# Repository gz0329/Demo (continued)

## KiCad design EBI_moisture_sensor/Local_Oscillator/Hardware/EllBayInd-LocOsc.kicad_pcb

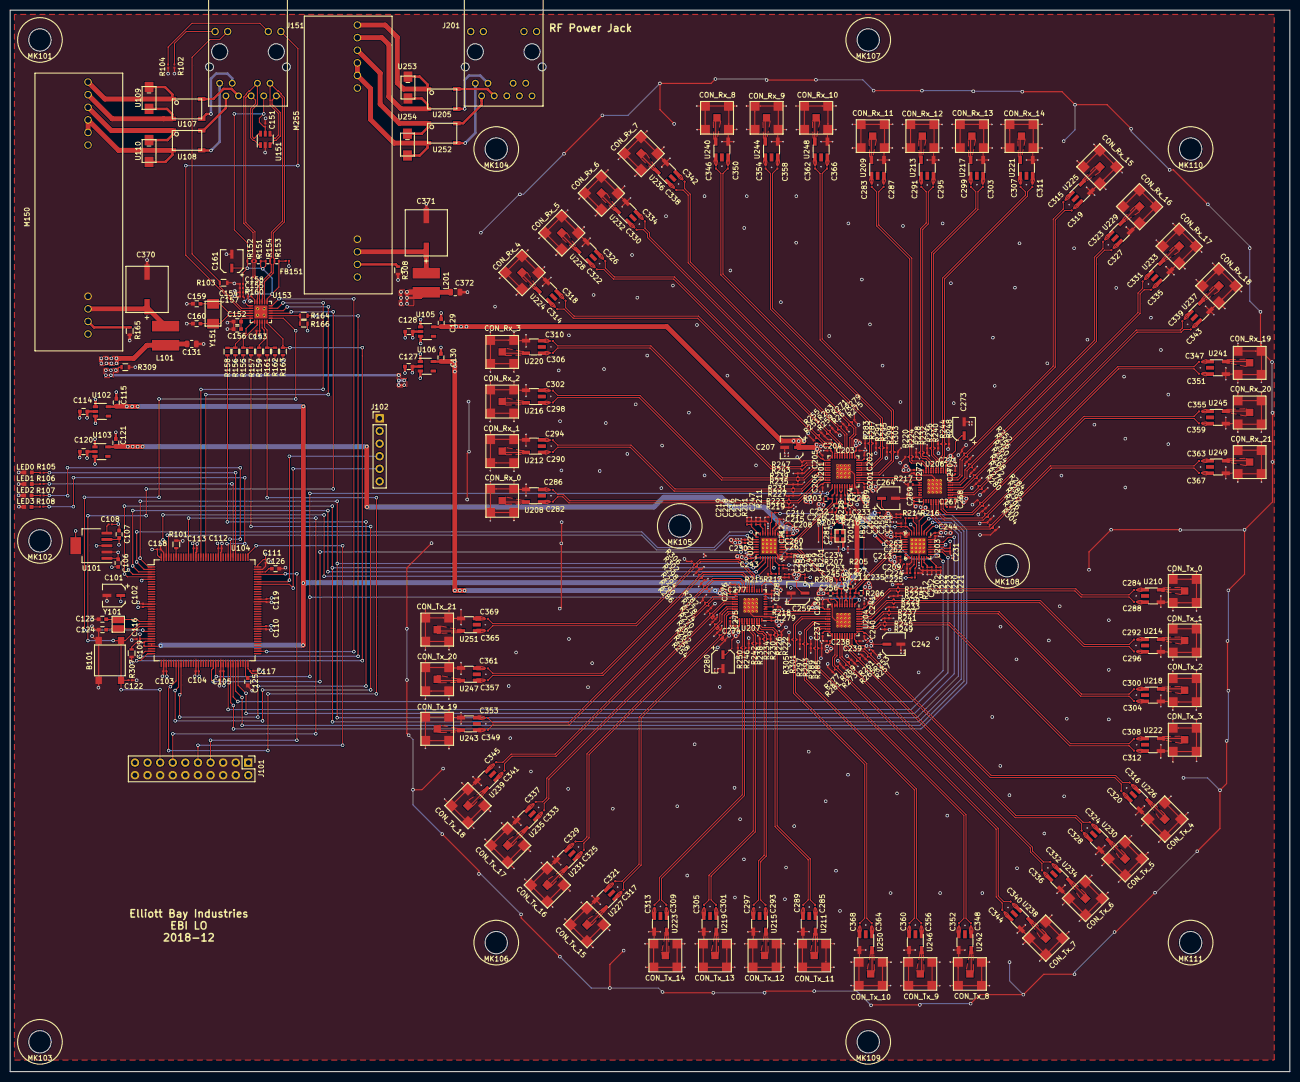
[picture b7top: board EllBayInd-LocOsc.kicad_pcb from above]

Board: 4 copper layers, 258.0 x 214.0 mm, 487 parts (0 on the bottom side), 356 nets.

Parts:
B101: Reset; Tactile_switch
C101, C161, C207, C242, C259, C264, C273, C280: 4.7uF; CP_Elec_4.3x4.3
C102, C103, C104, C105, C109, C110, C111, C112, C113, C116, C117, C118, C119, C122, C151, C153, C154, C155, C157, C158, C208, C209, C212, C213, C215, C217, C219, C220, C222, C224, C230, C231, C232, C235, C243, C244, C258, C261, C262, C265, C281: 100nF; C_0201_0603Metric
C106, C125, C126: 2.2uF; C_0603
C107, C114, C115, C120, C121, C127, C128, C129, C130, C156: 1uF; C_0603
C108: 0.01uF; C_0201_0603Metric
C123, C124: 4.3pF; C_0603
C131, C372: 10uF; C_0805_2012Metric
C152: 470pF; C_0603
C159, C160: 30pF; C_0603
C201, C202, C203, C204, C205, C206, C228, C229, C236, C237, C238, C239, C240, C241, C255, C256, C267, C268, C269, C270, C271, C272, C274, C275, C276, C277, C278, C279: 1nF; C_0201_0603Metric
C210, C211, C214, C216, C218, C221, C223, C225, C226, C227, C233, C234, C245, C246, C248, C251, C253, C254, C257, C260, C263, C266, C282, C283, C284, C285, C286, C287, C288, C289, C290, C291, C292, C293, C294, C295, C296, C297, C298, C299, C300, C301, C302, C303, C304, C305, C306, C307, C308, C309, C310, C311, C312, C313, C314, C315, C316, C317, C318, C319, C320, C321, C322, C323, C324, C325, C326, C327, C328, C329, C330, C331, C332, C333, C334, C335, C336, C337, C338, C339, C340, C341, C342, C343, C344, C345, C346, C347, C348, C349, C350, C351, C352, C353, C354, C355, C356, C357, C358, C359, C360, C361, C362, C363, C364, C365, C366, C367, C368, C369: 100pF; C_0201_0603Metric
C247, C252: 3.3pF; C_0201_0603Metric
C249, C250: 7.3pF; C_0201_0603Metric
C370, C371: 470uF; 470uF Cap
CON_Rx_0, CON_Rx_1, CON_Rx_2, CON_Rx_3, CON_Rx_4, CON_Rx_5, CON_Rx_6, CON_Rx_7, CON_Rx_8, CON_Rx_9, CON_Rx_10, CON_Rx_11, CON_Rx_12, CON_Rx_13, CON_Rx_14, CON_Rx_15, CON_Rx_16, CON_Rx_17, CON_Rx_18, CON_Rx_19, CON_Rx_20, CON_Rx_21: RF_SMA; SMAConnector
CON_Tx_0, CON_Tx_1, CON_Tx_2, CON_Tx_3, CON_Tx_4, CON_Tx_5, CON_Tx_6, CON_Tx_7, CON_Tx_8, CON_Tx_9, CON_Tx_10, CON_Tx_11, CON_Tx_12, CON_Tx_13, CON_Tx_14, CON_Tx_15, CON_Tx_16, CON_Tx_17, CON_Tx_18, CON_Tx_19, CON_Tx_20, CON_Tx_21: RF_SMA; SMAConnector
FB151, FB201, FB202: 600@100; L_0201_0603Metric
J101: SWD debugging; Program_Pin_Header
J102: Conn_01x06_UART1; PinHeader_1x06_P2.54mm_Vertical
J151, J201: RJ45_7499211122A; RJ45
L101, L201: 10uH; 10uH_Inductor
LED0, LED1, LED2, LED3: LED
M150, M255: AG9205S
MK101, MK102, MK103, MK104, MK105, MK106, MK107, MK108, MK109, MK110, MK111: Mounting_hole
R101, R103, R155, R156, R159, R162, R166: 10k; R_0603
R102, R104: 270; R_0201_0603Metric
R105, R106, R107, R108: 750; R_0201_0603Metric
R151, R152, R153, R154, R203, R204, R205, R206, R207, R208, R209, R210, R217, R218: 50; R_0402
R157, R158, R161, R164: 33; R_0603
R160: 12k1; R_0201_0603Metric
R163: 1k5; R_0603
R165, R308: 0; R_0603
R201, R202: 5.1k; R_0201_0603Metric
R211, R212: 91k; R_0201_0603Metric
R213, R214: 11.3k; R_0201_0603Metric
R215, R216: 33.2k; R_0201_0603Metric
R219, R220, R221, R222, R223, R224, R225, R226, R227, R228, R229, R230, R231, R232, R233, R234, R235, R236, R237, R238, R239, R240, R241, R242, R243, R244, R245, R246, R247, R248, R249, R250, R251, R252, R253, R254, R255, R256, R257, R258, R259, R260, R261, R262, R263, R264, R265, R266, R267, R268, R269, R270, R271, R272, R273, R274, R275, R276, R277, R278, R279, R280, R281, R282, R283, R284, R285, R286, R287, R288, R289, R290, R291, R292, R293, R294, R295, R296, R297, R298, R299, R300, R301, R302, R303, R304, R305, R306: 200; R_0201_0603Metric
R307, R309: Close; R_0603
U101: 5V_REG
U102, U103, U105, U106: 3V3_REG; 3V3REG
U104: STM32H743ZITx; MCU
U107, U108, U205, U252: MDB6S
U109, U110, U253, U254: SMAJ58CA
U151: USBLC6-4SC6; TVS-diode
U153: LAN8742A
U201, U204, U206, U207: ADCLK954
U202, U203: ADF4350
U208, U209, U210, U211, U212, U213, U214, U215, U216, U217, U218, U219, U220, U221, U222, U223, U224, U225, U226, U227, U228, U229, U230, U231, U232, U233, U234, U235, U236, U237, U238, U239, U240, U241, U242, U243, U244, U245, U246, U247, U248, U249, U250, U251: TC1-1-43+
Y101: 8 MHz; 8mhz_crystal
Y151: 25MHz; 25mhz_crystal
Y201: 24MHz; 24MhzCrystalOsc

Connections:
+3.3VA: C109.1, C115.1, FB201.1, FB202.1, U102.5, U104.32, U104.33, U202.16, U202.17, U203.16, U203.17
+3V3: C101.1, C102.1, C103.1, C104.1, C105.1, C110.1, C111.1, C112.1, C113.1, C116.1, C117.1, C118.1, C119.1, C121.1, C153.2, C208.1, C209.1, C212.1, C213.1, C230.1, C231.1, C232.1, C233.1, C234.1, C235.1, C243.1, C244.1, C281.1, FB151.2, J101.1, J101.2, R155.2, R156.2, R162.2, R163.2, R166.2, R203.2, R204.2, R205.2, R206.2, R207.1, R208.1, R209.1, R210.1, U103.5, U104.6, U104.17, U104.30, U104.39, U104.52, U104.62, U104.72, U104.84, U104.95, U104.108, U104.121, U104.131, U104.144, U153.9, U202.28, U202.32, U203.28, U203.32, Y201.4
+5V: C107.1, U101.4
/3.3V_FO_pair_0: C129.1, C201.1, C202.1, C203.1, C204.1, C205.1, C206.1, C207.1, C267.1, C268.1, C269.1, C270.1, C271.1, C272.1, C273.1, U105.5, U201.11, U201.20, U201.21, U201.30, U201.31, U201.40, U206.11, U206.20, U206.21, U206.30, U206.31, U206.40
/3.3V_FO_pair_1: C130.1, C236.1, C237.1, C238.1, C239.1, C240.1, C241.1, C242.1, C274.1, C275.1, C276.1, C277.1, C278.1, C279.1, C280.1, U106.5, U204.11, U204.20, U204.21, U204.30, U204.31, U204.40, U207.11, U207.20, U207.21, U207.30, U207.31, U207.40
/5.5V: C106.1, C114.1, C120.1, C131.2, L101.1, U101.1, U101.2, U102.1, U102.3, U103.1, U103.3
/5.5V_RF: C127.1, C128.1, C372.1, L201.1, U105.1, U105.3, U106.1, U106.3
/24MHz: U202.29, U203.29, Y201.3
/AVdd: C257.1, C258.1, C259.1, C260.1, C261.1, C262.1, C263.1, C264.1, C265.1, C266.1, FB201.2, FB202.2, U202.6, U202.10, U203.6, U203.10
/Common/CRS_DV: R161.2, U104.43
/Common/LED0: R105.2, U104.114
/Common/LED1: R106.2, U104.115
/Common/LED2: R107.2, U104.116
/Common/LED3: R108.2, U104.117
/Common/MDC: U104.27, U153.13
/Common/MDIO: R163.1, U104.36, U153.12
/Common/NRST: B101.3, B101.4, C122.1, J101.15, U104.25, U153.15
/Common/RX_D0: R157.2, U104.44
/Common/RX_D1: R158.2, U104.45
/Common/SWCLK: J101.9, U104.109
/Common/SWDIO: J101.7, U104.105
/Common/Sheet5C53D1CF/LED_G: J151.13, R103.1, U153.2
/Common/Sheet5C53D1CF/LED_Y: J151.11, U153.3
/Common/Sheet5C53D1CF/RX+: J151.4, R152.2, U151.6, U153.23
/Common/Sheet5C53D1CF/RX-: J151.5, R151.2, U151.1, U153.22
/Common/Sheet5C53D1CF/TX+: J151.1, R154.2, U151.3, U153.21
/Common/Sheet5C53D1CF/TX-: J151.2, R153.2, U151.4, U153.20
/Common/Sheet5C53D1CF/VC1+: J151.7, U107.4
/Common/Sheet5C53D1CF/VC1-: J151.8, U107.3
/Common/Sheet5C53D1CF/VC2+: J151.9, U108.4
/Common/Sheet5C53D1CF/VC2-: J151.10, U108.3
/Common/TRACESWO: J101.13, U104.133
/Common/TX_D0: U104.128, U153.17
/Common/TX_D1: U104.74, U153.18
/Common/TX_EN: U104.126, U153.16
/Common/UART1_RX: J102.4, U104.102
/Common/UART1_TX: J102.5, U104.101
/Common/nINT: R164.2, U104.35
/FIN0_N: C226.1, U201.2
/FIN0_P: C210.1, U201.3
/FIN1_N: C253.1, U204.6
/FIN1_P: C245.1, U204.7
/FIN2_N: C227.1, U204.2
/FIN2_P: C211.1, U204.3
/FIN3_N: C254.1, U201.6
/FIN3_P: C246.1, U201.7
/LO_RX_0_N: C286.2, R223.2, U201.38
/LO_RX_0_P: C282.2, R219.2, U201.39
/LO_RX_1_N: C294.2, R231.2, U201.36
/LO_RX_1_P: C290.2, R227.2, U201.37
/LO_RX_2_N: C302.2, R239.2, U201.34
/LO_RX_2_P: C298.2, R235.2, U201.35
/LO_RX_3_N: C310.2, R247.2, U201.32
/LO_RX_3_P: C306.2, R243.2, U201.33
/LO_RX_4_N: C318.2, R255.2, U201.28
/LO_RX_4_P: C314.2, R251.2, U201.29
/LO_RX_5_N: C326.2, R263.2, U201.26
/LO_RX_5_P: C322.2, R259.2, U201.27
/LO_RX_6_N: C334.2, R271.2, U201.24
/LO_RX_6_P: C330.2, R267.2, U201.25
/LO_RX_7_N: C342.2, R279.2, U201.22
/LO_RX_7_P: C338.2, R275.2, U201.23
/LO_RX_8_N: C350.2, R287.2, U201.18
/LO_RX_8_P: C346.2, R283.2, U201.19
/LO_RX_9_N: C358.2, R295.2, U201.16
/LO_RX_9_P: C354.2, R291.2, U201.17
/LO_RX_10_N: C366.2, R303.2, U201.14
/LO_RX_10_P: C362.2, R299.2, U201.15
/LO_RX_11_N: C287.2, R224.2, U206.38
/LO_RX_11_P: C283.2, R220.2, U206.39
/LO_RX_12_N: C295.2, R232.2, U206.36
/LO_RX_12_P: C291.2, R228.2, U206.37
/LO_RX_13_N: C303.2, R240.2, U206.34
/LO_RX_13_P: C299.2, R236.2, U206.35
/LO_RX_14_N: C311.2, R248.2, U206.32
/LO_RX_14_P: C307.2, R244.2, U206.33
/LO_RX_15_N: C319.2, R256.2, U206.28
/LO_RX_15_P: C315.2, R252.2, U206.29
/LO_RX_16_N: C327.2, R264.2, U206.26
/LO_RX_16_P: C323.2, R260.2, U206.27
/LO_RX_17_N: C335.2, R272.2, U206.24
/LO_RX_17_P: C331.2, R268.2, U206.25
/LO_RX_18_N: C343.2, R280.2, U206.22
/LO_RX_18_P: C339.2, R276.2, U206.23
/LO_RX_19_N: C351.2, R288.2, U206.18
/LO_RX_19_P: C347.2, R284.2, U206.19
/LO_RX_20_N: C359.2, R296.2, U206.16
/LO_RX_20_P: C355.2, R292.2, U206.17
/LO_RX_21_N: C367.2, R304.2, U206.14
/LO_RX_21_P: C363.2, R300.2, U206.15
/LO_TX_0_N: C288.2, R225.2, U204.38
/LO_TX_0_P: C284.2, R221.2, U204.39
/LO_TX_1_N: C296.2, R233.2, U204.36
/LO_TX_1_P: C292.2, R229.2, U204.37
/LO_TX_2_N: C304.2, R241.2, U204.34
/LO_TX_2_P: C300.2, R237.2, U204.35
/LO_TX_3_N: C312.2, R249.2, U204.32
/LO_TX_3_P: C308.2, R245.2, U204.33
/LO_TX_4_N: C320.2, R257.2, U204.28
/LO_TX_4_P: C316.2, R253.2, U204.29
/LO_TX_5_N: C328.2, R265.2, U204.26
/LO_TX_5_P: C324.2, R261.2, U204.27
/LO_TX_6_N: C336.2, R273.2, U204.24
/LO_TX_6_P: C332.2, R269.2, U204.25
/LO_TX_7_N: C344.2, R281.2, U204.22
/LO_TX_7_P: C340.2, R277.2, U204.23
/LO_TX_8_N: C352.2, R289.2, U204.18
/LO_TX_8_P: C348.2, R285.2, U204.19
/LO_TX_9_N: C360.2, R297.2, U204.16
/LO_TX_9_P: C356.2, R293.2, U204.17
/LO_TX_10_N: C368.2, R305.2, U204.14
/LO_TX_10_P: C364.2, R301.2, U204.15
/LO_TX_11_N: C289.2, R226.2, U207.38
/LO_TX_11_P: C285.2, R222.2, U207.39
/LO_TX_12_N: C297.2, R234.2, U207.36
/LO_TX_12_P: C293.2, R230.2, U207.37
/LO_TX_13_N: C305.2, R242.2, U207.34
/LO_TX_13_P: C301.2, R238.2, U207.35
/LO_TX_14_N: C313.2, R250.2, U207.32
/LO_TX_14_P: C309.2, R246.2, U207.33
/LO_TX_15_N: C321.2, R258.2, U207.28
/LO_TX_15_P: C317.2, R254.2, U207.29
/LO_TX_16_N: C329.2, R266.2, U207.26
/LO_TX_16_P: C325.2, R262.2, U207.27
/LO_TX_17_N: C337.2, R274.2, U207.24
/LO_TX_17_P: C333.2, R270.2, U207.25
/LO_TX_18_N: C345.2, R282.2, U207.22
/LO_TX_18_P: C341.2, R278.2, U207.23
/LO_TX_19_N: C353.2, R290.2, U207.18
/LO_TX_19_P: C349.2, R286.2, U207.19
/LO_TX_20_N: C361.2, R298.2, U207.16
/LO_TX_20_P: C357.2, R294.2, U207.17
/LO_TX_21_N: C369.2, R306.2, U207.14
/LO_TX_21_P: C365.2, R302.2, U207.15
/RF_VC1+: J201.7, U205.4
/RF_VC1-: J201.8, U205.3
/RF_VC2+: J201.9, U252.4
/RF_VC2-: J201.10, U252.3
/SEL_SYNTH_1: U104.59, U201.1, U204.1
/SPI4_MOSI: U104.5, U202.2, U203.2
/SPI4_SCK: U104.1, U202.1, U203.1
/SYNTH0_EN: U104.142, U202.4
/SYNTH0_LD: U104.2, U202.25
/SYNTH0_MUXOUT: U104.58, U202.30
/SYNTH1_EN: U104.65, U203.4
/SYNTH1_LD: U104.66, U203.25
/SYNTH1_MUXOUT: U104.68, U203.30
/Vtune0: C247.1, R211.1, U202.20
/Vtune1: C252.1, R212.1, U203.20
/~SYNTH0_CS: U104.3, U202.3
/~SYNTH0_PDBrf: U104.141, U202.26
/~SYNTH1_CS: U104.67, U203.3
/~SYNTH1_PDBrf: U104.64, U203.26
GND: B101.1, B101.2, C101.2, C102.2, C103.2, C104.2, C105.2, C110.2, C111.2, C112.2, C113.2, C116.2, C117.2, C118.2, C119.2, C122.2, C123.2, C124.2, C125.2, C126.2, C131.1, C151.1, C152.1, C153.1, C154.1, C155.1, C156.1, C157.1, C158.1, C159.1, C160.1, C161.2, C201.2, C202.2, C203.2, C204.2, C205.2, C206.2, C207.2, C208.2, C209.2, C212.2, C213.2, C214.2, C215.2, C216.2, C217.2, C218.2, C219.2, C220.2, C221.2, C222.2, C223.2, C224.2, C225.2, C228.1, C229.1, C230.2, C231.2, C232.2, C233.2, C234.2, C235.2, C236.2, C237.2, C238.2, C239.2, C240.2, C241.2, C242.2, C243.2, C244.2, C247.2, C249.2, C250.2, C252.2, C255.1, C256.1, C257.2, C258.2, C259.2, C260.2, C261.2, C262.2, C263.2, C264.2, C265.2, C266.2, C267.2, C268.2, C269.2, C270.2, C271.2, C272.2, C273.2, C274.2, C275.2, C276.2, C277.2, C278.2, C279.2, C280.2, C281.2, C370.2, C371.2, C372.2, CON_Rx_0.2, CON_Rx_1.2, CON_Rx_2.2, CON_Rx_3.2, CON_Rx_4.2, CON_Rx_5.2, CON_Rx_6.2, CON_Rx_7.2, CON_Rx_8.2, CON_Rx_9.2, CON_Rx_10.2, CON_Rx_11.2, CON_Rx_12.2, CON_Rx_13.2, CON_Rx_14.2, CON_Rx_15.2, CON_Rx_16.2, CON_Rx_17.2, CON_Rx_18.2, CON_Rx_19.2, CON_Rx_20.2, CON_Rx_21.2, CON_Tx_0.2, CON_Tx_1.2, CON_Tx_2.2, CON_Tx_3.2, CON_Tx_4.2, CON_Tx_5.2, CON_Tx_6.2, CON_Tx_7.2, CON_Tx_8.2, CON_Tx_9.2, CON_Tx_10.2, CON_Tx_11.2, CON_Tx_12.2, CON_Tx_13.2, CON_Tx_14.2, CON_Tx_15.2, CON_Tx_16.2, CON_Tx_17.2, CON_Tx_18.2, CON_Tx_19.2, CON_Tx_20.2, CON_Tx_21.2, J101.3, J101.4, J101.5, J101.6, J101.8, J101.10, J101.12, J101.14, J101.16, J101.18, J101.20, J102.1, LED0.1, LED1.1, LED2.1, LED3.1, M150.7, M255.7, R101.2, R102.2, R103.2, R104.2, R159.2, R160.1, R165.1, R201.1, R202.1, R215.1, R216.1, R217.2, R218.2, R219.1, R220.1, R221.1, R222.1, R223.1, R224.1, R225.1, R226.1, R227.1, R228.1, R229.1, R230.1, R231.1, R232.1, R233.1, R234.1, R235.1, R236.1, R237.1, R238.1, R239.1, R240.1, R241.1, R242.1, R243.1, R244.1, R245.1, R246.1, R247.1, R248.1, R249.1, R250.1, R251.1, R252.1, R253.1, R254.1, R255.1, R256.1, R257.1, R258.1, R259.1, R260.1, R261.1, R262.1, R263.1, R264.1, R265.1, R266.1, R267.1, R268.1, R269.1, R270.1, R271.1, R272.1, R273.1, R274.1, R275.1, R276.1, R277.1, R278.1, R279.1, R280.1, R281.1, R282.1, R283.1, R284.1, R285.1, R286.1, R287.1, R288.1, R289.1, R290.1, R291.1, R292.1, R293.1, R294.1, R295.1, R296.1, R297.1, R298.1, R299.1, R300.1, R301.1, R302.1, R303.1, R304.1, R305.1, R306.1, R307.2, R308.2, R309.1, U104.16, U104.38, U104.51, U104.61, U104.83, U104.94, U104.107, U104.120, U104.130, U104.143, U151.2, U153.25, U201.10, U201.41, U202.8, U202.9, U202.11, U202.18, U202.21, U202.27, U202.31, U202.33, U203.8, U203.9, U203.11, U203.18, U203.21, U203.27, U203.31, U203.33, U204.10, U204.41, U206.1, U206.10, U206.41, U207.1, U207.10, U207.41, U208.4, U209.4, U210.4, U211.4, U212.4, U213.4, U214.4, U215.4, U216.4, U217.4, U218.4, U219.4, U220.4, U221.4, U222.4, U223.4, U224.4, U225.4, U226.4, U227.4, U228.4, U229.4, U230.4, U231.4, U232.4, U233.4, U234.4, U235.4, U236.4, U237.4, U238.4, U239.4, U240.4, U241.4, U242.4, U243.4, U244.4, U245.4, U246.4, U247.4, U248.4, U249.4, U250.4, U251.4, Y201.2
GNDA: C109.2, R307.1, U104.31
GNDPWR: C106.2, C107.2, C108.2, C114.2, C115.2, C120.2, C121.2, C127.2, C128.2, C129.2, C130.2, R309.2, U101.3, U101.6, U102.2, U103.2, U105.2, U106.2
unnamed: C108.1, U101.5
unnamed: C123.1, U104.23, Y101.1
unnamed: C124.1, U104.24, Y101.2
unnamed: C125.1, U104.71
unnamed: C126.1, U104.106
unnamed: C151.2, C154.2, C155.2, C157.2, C158.2, C161.1, FB151.1, J151.3, R151.1, R152.1, R153.1, R154.1, U151.5, U153.1, U153.19
unnamed: C152.2, C156.2, U153.6
unnamed: C159.2, U153.4, Y151.2
unnamed: C160.2, U153.5, Y151.1
unnamed: C210.2, R204.1, U202.14
unnamed: C211.2, R205.1, U203.14
unnamed: C214.1, C215.1, U202.19
unnamed: C216.1, C217.1, U202.23
unnamed: C218.1, C219.1, U202.24
unnamed: C220.1, C221.1, U203.24
unnamed: C222.1, C223.1, U203.23
unnamed: C224.1, C225.1, U203.19
unnamed: C226.2, R203.1, U202.15
unnamed: C227.2, R206.1, U203.15
unnamed: C228.2, U201.4, U201.5
unnamed: C229.2, U201.8, U201.9
unnamed: C245.2, R208.2, U202.12
unnamed: C246.2, R209.2, U203.12
unnamed: C248.1, C249.1, R211.2, U202.7
unnamed: C248.2, R213.2
unnamed: C250.1, C251.1, R212.2, U203.7
unnamed: C251.2, R214.2
unnamed: C253.2, R207.2, U202.13
unnamed: C254.2, R210.2, U203.13
unnamed: C255.2, U204.4, U204.5
unnamed: C256.2, U204.8, U204.9
unnamed: C282.1, U208.1
unnamed: C283.1, U209.1
unnamed: C284.1, U210.1
unnamed: C285.1, U211.1
unnamed: C286.1, U208.3
unnamed: C287.1, U209.3
unnamed: C288.1, U210.3
unnamed: C289.1, U211.3
unnamed: C290.1, U212.1
unnamed: C291.1, U213.1
unnamed: C292.1, U214.1
unnamed: C293.1, U215.1
unnamed: C294.1, U212.3
unnamed: C295.1, U213.3
unnamed: C296.1, U214.3
unnamed: C297.1, U215.3
unnamed: C298.1, U216.1
unnamed: C299.1, U217.1
unnamed: C300.1, U218.1
unnamed: C301.1, U219.1
unnamed: C302.1, U216.3
unnamed: C303.1, U217.3
unnamed: C304.1, U218.3
unnamed: C305.1, U219.3
unnamed: C306.1, U220.1
unnamed: C307.1, U221.1
unnamed: C308.1, U222.1
unnamed: C309.1, U223.1
unnamed: C310.1, U220.3
unnamed: C311.1, U221.3
unnamed: C312.1, U222.3
unnamed: C313.1, U223.3
unnamed: C314.1, U224.1
unnamed: C315.1, U225.1
unnamed: C316.1, U226.1
unnamed: C317.1, U227.1
unnamed: C318.1, U224.3
unnamed: C319.1, U225.3
unnamed: C320.1, U226.3
unnamed: C321.1, U227.3
unnamed: C322.1, U228.1
unnamed: C323.1, U229.1
unnamed: C324.1, U230.1
unnamed: C325.1, U231.1
unnamed: C326.1, U228.3
unnamed: C327.1, U229.3
unnamed: C328.1, U230.3
unnamed: C329.1, U231.3
unnamed: C330.1, U232.1
unnamed: C331.1, U233.1
unnamed: C332.1, U234.1
unnamed: C333.1, U235.1
unnamed: C334.1, U232.3
unnamed: C335.1, U233.3
unnamed: C336.1, U234.3
unnamed: C337.1, U235.3
unnamed: C338.1, U236.1
unnamed: C339.1, U237.1
unnamed: C340.1, U238.1
unnamed: C341.1, U239.1
unnamed: C342.1, U236.3
unnamed: C343.1, U237.3
unnamed: C344.1, U238.3
unnamed: C345.1, U239.3
unnamed: C346.1, U240.1
unnamed: C347.1, U241.1
unnamed: C348.1, U242.1
unnamed: C349.1, U243.1
unnamed: C350.1, U240.3
unnamed: C351.1, U241.3
unnamed: C352.1, U242.3
unnamed: C353.1, U243.3
unnamed: C354.1, U244.1
unnamed: C355.1, U245.1
unnamed: C356.1, U246.1
unnamed: C357.1, U247.1
unnamed: C358.1, U244.3
unnamed: C359.1, U245.3
unnamed: C360.1, U246.3
unnamed: C361.1, U247.3
unnamed: C362.1, U248.1
unnamed: C363.1, U249.1
unnamed: C364.1, U250.1
unnamed: C365.1, U251.1
unnamed: C366.1, U248.3
unnamed: C367.1, U249.3
unnamed: C368.1, U250.3
unnamed: C369.1, U251.3
unnamed: C370.1, L101.2, M150.8
unnamed: C371.1, L201.2, M255.8
unnamed: CON_Rx_0.1, U208.6
unnamed: CON_Rx_1.1, U212.6
unnamed: CON_Rx_2.1, U216.6
unnamed: CON_Rx_3.1, U220.6
unnamed: CON_Rx_4.1, U224.6
unnamed: CON_Rx_5.1, U228.6
unnamed: CON_Rx_6.1, U232.6
unnamed: CON_Rx_7.1, U236.6
unnamed: CON_Rx_8.1, U240.6
unnamed: CON_Rx_9.1, U244.6
unnamed: CON_Rx_10.1, U248.6
unnamed: CON_Rx_11.1, U209.6
unnamed: CON_Rx_12.1, U213.6
unnamed: CON_Rx_13.1, U217.6
unnamed: CON_Rx_14.1, U221.6
unnamed: CON_Rx_15.1, U225.6
unnamed: CON_Rx_16.1, U229.6
unnamed: CON_Rx_17.1, U233.6
unnamed: CON_Rx_18.1, U237.6
unnamed: CON_Rx_19.1, U241.6
unnamed: CON_Rx_20.1, U245.6
unnamed: CON_Rx_21.1, U249.6
unnamed: CON_Tx_0.1, U210.6
unnamed: CON_Tx_1.1, U214.6
unnamed: CON_Tx_2.1, U218.6
unnamed: CON_Tx_3.1, U222.6
unnamed: CON_Tx_4.1, U226.6
unnamed: CON_Tx_5.1, U230.6
unnamed: CON_Tx_6.1, U234.6
unnamed: CON_Tx_7.1, U238.6
unnamed: CON_Tx_8.1, U242.6
unnamed: CON_Tx_9.1, U246.6
unnamed: CON_Tx_10.1, U250.6
unnamed: CON_Tx_11.1, U211.6
unnamed: CON_Tx_12.1, U215.6
unnamed: CON_Tx_13.1, U219.6
unnamed: CON_Tx_14.1, U223.6
unnamed: CON_Tx_15.1, U227.6
unnamed: CON_Tx_16.1, U231.6
unnamed: CON_Tx_17.1, U235.6
unnamed: CON_Tx_18.1, U239.6
unnamed: CON_Tx_19.1, U243.6
unnamed: CON_Tx_20.1, U247.6
unnamed: CON_Tx_21.1, U251.6
unnamed: J151.12, R104.1
unnamed: J151.14, R102.1
unnamed: M150.1, U107.1, U109.1
unnamed: M150.2, U107.2, U109.2
unnamed: M150.3, U108.1, U110.1
unnamed: M150.4, M150.5, U108.2, U110.2
unnamed: M150.9, R165.2
unnamed: M255.1, U205.1, U253.1
unnamed: M255.2, U205.2, U253.2
unnamed: M255.3, U252.1, U254.1
unnamed: M255.4, M255.5, U252.2, U254.2
unnamed: M255.9, R308.1
unnamed: R101.1, U104.138
unnamed: LED0.2, R105.1
unnamed: LED1.2, R106.1
unnamed: LED2.2, R107.1
unnamed: LED3.2, R108.1
unnamed: R155.1, R157.1, U153.8
unnamed: R156.1, R158.1, U153.7
unnamed: R159.1, U153.10
unnamed: R160.2, U153.24
unnamed: R161.1, R162.1, U153.11
unnamed: R164.1, R166.1, U153.14
unnamed: R201.2, U202.22
unnamed: R202.2, U203.22
unnamed: R213.1, R215.2, U202.5
unnamed: R214.1, R216.2, U203.5
unnamed: R217.1, U206.4, U206.5
unnamed: R218.1, U207.4, U207.5
unnamed: U201.12, U206.3
unnamed: U201.13, U206.2
unnamed: U204.12, U207.3
unnamed: U204.13, U207.2
unnamed: U206.8, U206.9
unnamed: U207.8, U207.9

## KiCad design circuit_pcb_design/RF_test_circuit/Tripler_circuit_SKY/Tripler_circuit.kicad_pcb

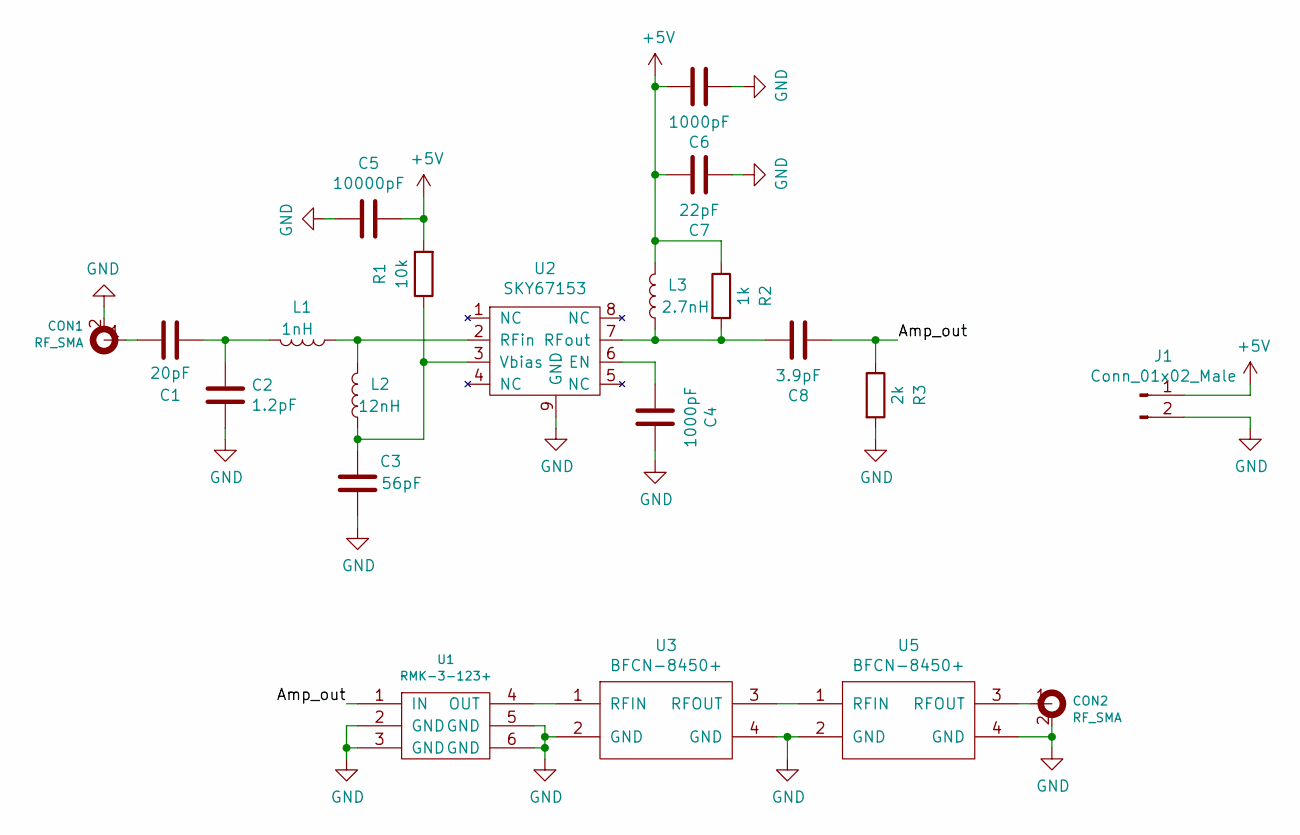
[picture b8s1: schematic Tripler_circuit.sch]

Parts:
C1: 20pF; C_0402
C2: 1.2pF; C_0402
C3: 56pF; C_0402
C4, C6: 1000pF; C_0402
C5: 10000pF; C_0402
C7: 22pF; C_0402
C8: 3.9pF; C_0402
CON1, CON2: RF_SMA; SMAConnector
J1: Conn_01x02_Male; PinHeader_1x02_P2.54mm_Vertical
L1: 1nH; L_0402
L2: 12nH; L_0402
L3: 2.7nH; L_0402
R1: 10k; R_0402
R2: 1k; R_0402
R3: 2k; R_0402
U1: RMK-3-123+
U2: SKY67153
U3, U5: BFCN-8450+

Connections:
+5V: C5.1, C6.1, C7.1, J1.1, L3.2, R1.2, R2.1
/Amp_out: C8.2, R3.1, U1.1 (IN)
GND: C2.1, C3.1, C4.1, C5.2, C6.2, C7.2, CON1.2, CON2.2, J1.2, R3.2, U1.2 (GND), U1.3 (GND), U1.5 (GND), U1.6 (GND), U2.9 (GND), U3.2 (GND), U3.4 (GND), U5.2 (GND), U5.4 (GND)
unnamed: C1.1, C2.2, L1.2
unnamed: C1.2, CON1.1
unnamed: C3.2, L2.1, R1.1, U2.3 (Vbias)
unnamed: C4.2, U2.6 (EN)
unnamed: C8.1, L3.1, R2.2, U2.7 (RFout)
unnamed: CON2.1, U5.3 (RFOUT)
unnamed: L1.1, L2.2, U2.2 (RFin)
unnamed: U1.4 (OUT), U3.1 (RFIN)
unnamed: U3.3 (RFOUT), U5.1 (RFIN)

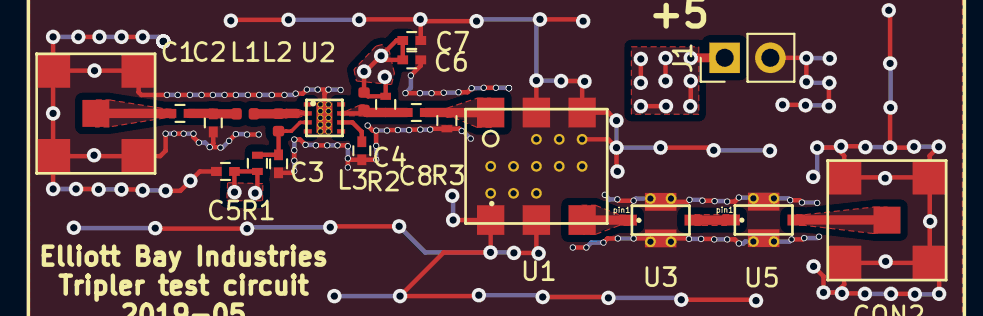
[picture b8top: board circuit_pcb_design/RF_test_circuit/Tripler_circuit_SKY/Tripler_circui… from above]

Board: 4 copper layers, 21 parts (0 on the bottom side), 12 nets.

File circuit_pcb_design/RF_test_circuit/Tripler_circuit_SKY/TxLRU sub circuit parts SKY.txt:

TxLRU sub circuit parts SKY

Amplifier
https://www.digikey.com/product-detail/en/skyworks-solutions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

2k res 0402
https://www.digikey.com/product-detail/en/yageo/RT0402BRD072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

1k res 0402
https://www.digikey.com/product-detail/en/yageo/RC0402JR-071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

10k res 0402
https://www.digikey.com/product-detail/en/yageo/RT0402BRD071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

20pF cap 0402
https://www.digikey.com/product-detail/en/yageo/CC0402JRNPO9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

1.2pF cap 0402
https://www.digikey.com/product-detail/en/yageo/CC0402BRNPO9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

3.9pF cap 0402
https://www.digikey.com/product-detail/en/yageo/CC0402CRNPO9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

56pF cap 0402
https://www.digikey.com/product-detail/en/yageo/CC0402JRNPO9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

10000pF cap 0402
https://www.digikey.com/product-detail/en/yageo/CC0402KRX7R8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

1000pF cap 0402
https://www.digikey.com/product-detail/en/yageo/CC0402KRX7R9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

22pF cap 0402
https://www.digikey.com/product-detail/en/yageo/CC0402JRNPO9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

2.7nH ind 0402
https://www.digikey.com/product-detail/en/taiyo-yuden/HK1005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

1nH ind 0402
https://www.digikey.com/product-detail/en/taiyo-yuden/HK1005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

12nH ind 0402
https://www.digikey.com/product-detail/en/taiyo-yuden/HK1005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

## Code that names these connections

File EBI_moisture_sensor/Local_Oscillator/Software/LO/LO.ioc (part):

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Mcu.Name=STM32H743ZITx
Mcu.Package=LQFP144
Mcu.UserName=STM32H743ZITx
PA1.GPIOParameters=GPIO_Label
PA1.GPIO_Label=RMII_REF_CLK
PA1.Mode=RMII
PA1.Signal=ETH_REF_CLK
PA13.GPIOParameters=GPIO_Label
PA13.GPIO_Label=TMS
PA13.Mode=Serial_Wire
PA13.Signal=SYS_JTMS-SWDIO
PA14.GPIOParameters=GPIO_Label
PA14.GPIO_Label=TCK
PA14.Mode=Serial_Wire
PA14.Signal=SYS_JTCK-SWCLK
PA2.GPIOParameters=GPIO_Label
PA2.GPIO_Label=RMII_MDIO
PA2.Mode=RMII
PA2.Signal=ETH_MDIO
PA7.GPIOParameters=GPIO_Label
PA7.GPIO_Label=RMII_CRS_DV
PA7.Mode=RMII
PA7.Signal=ETH_CRS_DV
PB13.GPIOParameters=GPIO_Label
PB13.GPIO_Label=RMII_TXD1
PB13.Mode=RMII
PB13.Signal=ETH_TXD1
PB14.GPIOParameters=PinState,GPIO_Label
PB14.GPIO_Label=LD3 [Red]
PB14.PinState=GPIO_PIN_SET
PB14.Signal=GPIO_Output
PB7.GPIOParameters=PinState,GPIO_Label
PB7.GPIO_Label=LD2 [Blue]
PB7.PinState=GPIO_PIN_SET
PB7.Signal=GPIO_Output
PC1.GPIOParameters=GPIO_Label
PC1.GPIO_Label=RMII_MDC
PC1.Mode=RMII
PC1.Signal=ETH_MDC
PC13.GPIOParameters=GPIO_Label
PC13.GPIO_Label=USER_Btn [B1]
PC13.Signal=GPXTI13
PC4.GPIOParameters=GPIO_Label
PC4.GPIO_Label=RMII_RXD0
PC4.Mode=RMII
PC4.Signal=ETH_RXD0
PC5.GPIOParameters=GPIO_Label
PC5.GPIO_Label=RMII_RXD1
PC5.Mode=RMII
PC5.Signal=ETH_RXD1
PD8.GPIOParameters=GPIO_Label
PD8.GPIO_Label=STLK_RX [STM32F103CBT6_PA3]
PD8.Mode=Asynchronous
PD8.Signal=USART3_TX
PD9.GPIOParameters=GPIO_Label
PD9.GPIO_Label=STLK_TX [STM32F103CBT6_PA2]
PD9.Mode=Asynchronous
PD9.Signal=USART3_RX
PE0.GPIOParameters=GPIO_Label
PE0.GPIO_Label=SYNTH0_PDBrf
PE0.Signal=GPIO_Output
PE1.GPIOParameters=GPIO_Label
PE1.GPIO_Label=SYNTH0_EN
PE1.Signal=GPIO_Output
PE11.GPIOParameters=GPIO_Label
PE11.GPIO_Label=SYNTH1_PDBrf
PE11.Signal=GPIO_Output
PE12.GPIOParameters=GPIO_Label
PE12.GPIO_Label=SYNTH1_EN
PE12.Signal=GPIO_Output
PE13.GPIOParameters=GPIO_Label
PE13.GPIO_Label=SYNTH1_LD
PE13.Signal=GPIO_Input
PE14.GPIOParameters=GPIO_Label
PE14.GPIO_Label=SYNTH1_CS
PE14.Signal=GPIO_Output
PE15.GPIOParameters=GPIO_Label
PE15.GPIO_Label=SYNTH1_MUXOUT
PE15.Signal=GPIO_Input
PE2.GPIOParameters=GPIO_PuPd
PE2.GPIO_PuPd=GPIO_PULLDOWN
PE2.Mode=Full_Duplex_Master
PE2.Signal=SPI4_SCK
PE3.GPIOParameters=GPIO_Label
PE3.GPIO_Label=SYNTH0_LD
PE3.Signal=GPIO_Input
PE4.GPIOParameters=GPIO_Label
PE4.GPIO_Label=SYNTH0_CS
PE4.Signal=GPIO_Output
PE5.Mode=Full_Duplex_Master
PE5.Signal=SPI4_MISO
PE6.Mode=Full_Duplex_Master
PE6.Signal=SPI4_MOSI
PE7.GPIOParameters=GPIO_Label
PE7.GPIO_Label=SYNTH0_MUXOUT
PE7.Signal=GPIO_Input
PE8.GPIOParameters=GPIO_Label
PE8.GPIO_Label=SEL_SYNTH_0
PE8.Signal=GPIO_Output
PF12.Signal=GPIO_Output
PG11.GPIOParameters=GPIO_Label
PG11.GPIO_Label=RMII_TX_EN
PG11.Mode=RMII
PG11.Signal=ETH_TX_EN
PG13.GPIOParameters=GPIO_Label
PG13.GPIO_Label=RMII_TXD0
PG13.Mode=RMII
PG13.Signal=ETH_TXD0
PG6.GPIOParameters=GPIO_Label
PG6.GPIO_Label=USB_PowerSwitchOn [STMPS2151STR_EN]
PG6.Signal=GPIO_Output
PG7.GPIOParameters=GPIO_Label
PG7.GPIO_Label=USB_OverCurrent [STMPS2151STR_FAULT]
PG7.Signal=GPIO_Input
PH0-OSC_IN.GPIOParameters=GPIO_Label
PH0-OSC_IN.GPIO_Label=MCO
PH0-OSC_IN.Mode=HSE-External-Oscillator
PH0-OSC_IN.Signal=RCC_OSC_IN
PH1-OSC_OUT.Mode=HSE-External-Oscillator
PH1-OSC_OUT.Signal=RCC_OSC_OUT
RCC.HSE_VALUE=8000000
RCC.SYSCLKFreq_VALUE=384000000
RCC.SYSCLKSource=RCC_SYSCLKSOURCE_PLLCLK
RCC.SYSCLKSourceVirtual=RCC_SYSCLKSOURCE_PLLCLK
board=NUCLEO-H743ZI
boardIOC=true

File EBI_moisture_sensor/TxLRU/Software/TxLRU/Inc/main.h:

/**
  ******************************************************************************
  * @file           : main.h
  * @brief          : Header for main.c file.
  *                   This file contains the common defines of the application.
  ******************************************************************************
  * This notice applies to any and all portions of this file
  * that are not between comment pairs USER CODE BEGIN and
  * USER CODE END. Other portions of this file, whether 
  * inserted by the user or by software development tools
  * are owned by their respective copyright owners.
  *
  * Copyright (c) 2019 STMicroelectronics International N.V. 
  * All rights reserved.
  *
  * Redistribution and use in source and binary forms, with or without 
  * modification, are permitted, provided that the following conditions are met:
  *
  * 1. Redistribution of source code must retain the above copyright notice, 
  *    this list of conditions and the following disclaimer.
  * 2. Redistributions in binary form must reproduce the above copyright notice,
  *    this list of conditions and the following disclaimer in the documentation
  *    and/or other materials provided with the distribution.
  * 3. Neither the name of STMicroelectronics nor the names of other 
  *    contributors to this software may be used to endorse or promote products 
  *    derived from this software without specific written permission.
  * 4. This software, including modifications and/or derivative works of this 
  *    software, must execute solely and exclusively on microcontroller or
  *    microprocessor devices manufactured by or for STMicroelectronics.
  * 5. Redistribution and use of this software other than as permitted under 
  *    this license is void and will automatically terminate your rights under 
  *    this license. 
  *
  * THIS SOFTWARE IS PROVIDED BY STMICROELECTRONICS AND CONTRIBUTORS "AS IS" 
  * AND ANY EXPRESS, IMPLIED OR STATUTORY WARRANTIES, INCLUDING, BUT NOT 
  * LIMITED TO, THE IMPLIED WARRANTIES OF MERCHANTABILITY, FITNESS FOR A 
  * PARTICULAR PURPOSE AND NON-INFRINGEMENT OF THIRD PARTY INTELLECTUAL PROPERTY
  * RIGHTS ARE DISCLAIMED TO THE FULLEST EXTENT PERMITTED BY LAW. IN NO EVENT 
  * SHALL STMICROELECTRONICS OR CONTRIBUTORS BE LIABLE FOR ANY DIRECT, INDIRECT,
  * INCIDENTAL, SPECIAL, EXEMPLARY, OR CONSEQUENTIAL DAMAGES (INCLUDING, BUT NOT
  * LIMITED TO, PROCUREMENT OF SUBSTITUTE GOODS OR SERVICES; LOSS OF USE, DATA, 
  * OR PROFITS; OR BUSINESS INTERRUPTION) HOWEVER CAUSED AND ON ANY THEORY OF 
  * LIABILITY, WHETHER IN CONTRACT, STRICT LIABILITY, OR TORT (INCLUDING 
  * NEGLIGENCE OR OTHERWISE) ARISING IN ANY WAY OUT OF THE USE OF THIS SOFTWARE,
  * EVEN IF ADVISED OF THE POSSIBILITY OF SUCH DAMAGE.
  *
  ******************************************************************************
  */

/* Define to prevent recursive inclusion -------------------------------------*/
#ifndef __MAIN_H__
#define __MAIN_H__

/* Includes ------------------------------------------------------------------*/

/* USER CODE BEGIN Includes */
#include "cmsis_os.h"
#include <stdint.h>
#include <stdbool.h>
/* USER CODE END Includes */

/* Private define ------------------------------------------------------------*/

#define USER_Btn_Pin GPIO_PIN_13
#define USER_Btn_GPIO_Port GPIOC
#define MCO_Pin GPIO_PIN_0
#define MCO_GPIO_Port GPIOH
#define RMII_MDC_Pin GPIO_PIN_1
#define RMII_MDC_GPIO_Port GPIOC
#define RMII_REF_CLK_Pin GPIO_PIN_1
#define RMII_REF_CLK_GPIO_Port GPIOA
#define RMII_MDIO_Pin GPIO_PIN_2
#define RMII_MDIO_GPIO_Port GPIOA
#define RMII_CRS_DV_Pin GPIO_PIN_7
#define RMII_CRS_DV_GPIO_Port GPIOA
#define RMII_RXD0_Pin GPIO_PIN_4
#define RMII_RXD0_GPIO_Port GPIOC
#define RMII_RXD1_Pin GPIO_PIN_5
#define RMII_RXD1_GPIO_Port GPIOC
#define Switch_0_Pin GPIO_PIN_11
#define Switch_0_GPIO_Port GPIOE
#define Switch_1_Pin GPIO_PIN_12
#define Switch_1_GPIO_Port GPIOE
#define Switch_2_Pin GPIO_PIN_13
#define Switch_2_GPIO_Port GPIOE
#define Switch_3_Pin GPIO_PIN_14
#define Switch_3_GPIO_Port GPIOE
#define RMII_TXD1_Pin GPIO_PIN_13
#define RMII_TXD1_GPIO_Port GPIOB
#define LD3_Pin GPIO_PIN_14
#define LD3_GPIO_Port GPIOB
#define STLK_RX_Pin GPIO_PIN_8
#define STLK_RX_GPIO_Port GPIOD
#define STLK_TX_Pin GPIO_PIN_9
#define STLK_TX_GPIO_Port GPIOD
#define USB_PowerSwitchOn_Pin GPIO_PIN_6
#define USB_PowerSwitchOn_GPIO_Port GPIOG
#define USB_OverCurrent_Pin GPIO_PIN_7
#define USB_OverCurrent_GPIO_Port GPIOG
#define TMS_Pin GPIO_PIN_13
#define TMS_GPIO_Port GPIOA
#define TCK_Pin GPIO_PIN_14
#define TCK_GPIO_Port GPIOA
#define RMII_TX_EN_Pin GPIO_PIN_11
#define RMII_TX_EN_GPIO_Port GPIOG
#define RMII_TXD0_Pin GPIO_PIN_13
#define RMII_TXD0_GPIO_Port GPIOG
#define LD2_Pin GPIO_PIN_7
#define LD2_GPIO_Port GPIOB

/* ########################## Assert Selection ############################## */
/**
  * @brief Uncomment the line below to expanse the "assert_param" macro in the 
  *        HAL drivers code
  */
 #define USE_FULL_ASSERT    1U 

/* USER CODE BEGIN Private defines */
osThreadId MQTTTaskHandle;
osThreadId CellSequenceTaskHandle;

// Counter_us is for a high speed count down/ one shot timer
// When Is_counting is false, the task can write a new count down time.
// When Is_counting is true, the interrupt decrements the count down time every us.
volatile uint32_t Counter_us;
volatile bool Is_counting;

volatile uint32_t Timer1_counter_us;
/* USER CODE END Private defines */

#ifdef __cplusplus
 extern "C" {
#endif
void _Error_Handler(char *, int);

#define Error_Handler() _Error_Handler(__FILE__, __LINE__)
#ifdef __cplusplus
}
#endif

#endif /* __MAIN_H__ */

/************************ (C) COPYRIGHT STMicroelectronics *****END OF FILE****/

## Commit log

2019-08-13 Added demo projects.
2020-02-13 More script works
    The BoM one can automatically generate BoM file once related fields and values are added in the parts.
    The two serial ones are for some overnight tests where data need to be stored in a text file, then move them into an excel and create the chart.
2020-03-07 `vallen` is verified to be less than `len`, therefore, it can never be the case that `vallen >= len + sizeof(rhostname)`.
    This PR fixes the check so the `rhostname` array does not overflow.
    Reported-by: Github Security Lab <securitylab@github.com>
